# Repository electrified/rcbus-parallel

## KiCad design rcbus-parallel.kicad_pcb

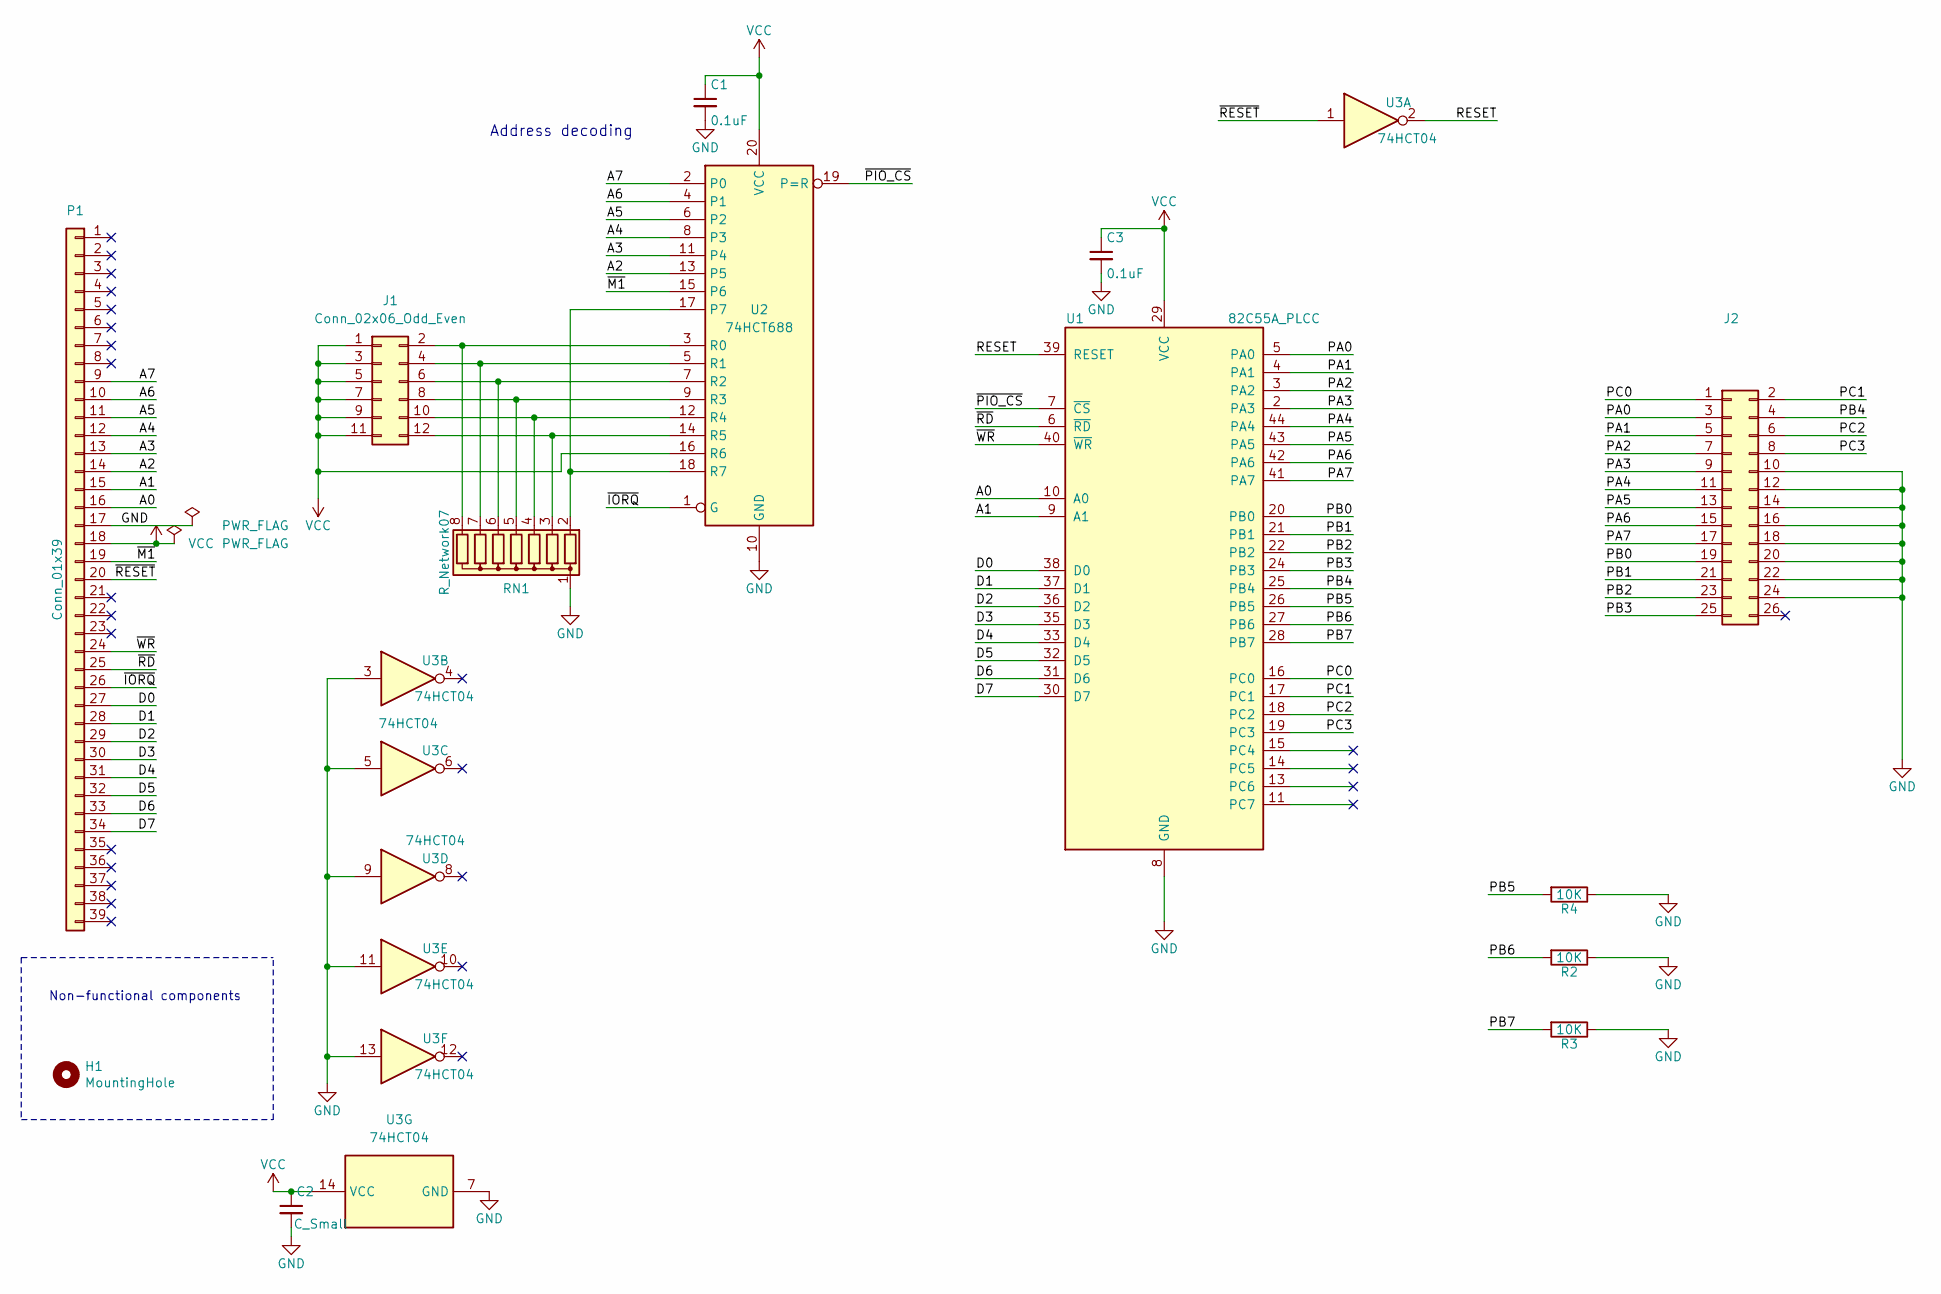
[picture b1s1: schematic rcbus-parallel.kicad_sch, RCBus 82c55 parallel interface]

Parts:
C1, C3: 0.1uF; C_Disc_D3.8mm_W2.6mm_P2.50mm
C2: C_Small; C_Disc_D3.8mm_W2.6mm_P2.50mm
H1: MountingHole; MountingHole_3.2mm_M3
J1: Conn_02x06_Odd_Even; PinHeader_2x06_P2.54mm_Vertical
J2: Conn_02x20_Odd_Even; IDC-Header_2x13_P2.54mm_Horizontal
P1: Conn_01x39; PinHeader_1x39_P2.54mm_Vertical
R2, R3, R4: 10K; R_Axial_DIN0207_L6.3mm_D2.5mm_P7.62mm_Horizontal
RN1: R_Network07; R_Array_SIP8
U1: 82C55A_PLCC; PLCC-44_THT-Socket
U2: 74HCT688; DIP-20_W7.62mm_Socket
U3: 74HCT04; DIP-14_W7.62mm_Socket

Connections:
/A0: P1.16, U1.10 (A0)
/A1: P1.15, U1.9 (A1)
/A2: P1.14, U2.13 (P5)
/A3: P1.13, U2.11 (P4)
/A4: P1.12, U2.8 (P3)
/A5: P1.11, U2.6 (P2)
/A6: P1.10, U2.4 (P1)
/A7: P1.9, U2.2 (P0)
/D0: P1.27, U1.38 (D0)
/D1: P1.28, U1.37 (D1)
/D2: P1.29, U1.36 (D2)
/D3: P1.30, U1.35 (D3)
/D4: P1.31, U1.33 (D4)
/D5: P1.32, U1.32 (D5)
/D6: P1.33, U1.31 (D6)
/D7: P1.34, U1.30 (D7)
/PA0: J2.3, U1.5 (PA0)
/PA1: J2.5, U1.4 (PA1)
/PA2: J2.7, U1.3 (PA2)
/PA3: J2.9, U1.2 (PA3)
/PA4: J2.11, U1.44 (PA4)
/PA5: J2.13, U1.43 (PA5)
/PA6: J2.15, U1.42 (PA6)
/PA7: J2.17, U1.41 (PA7)
/PB0: J2.19, U1.20 (PB0)
/PB1: J2.21, U1.21 (PB1)
/PB2: J2.23, U1.22 (PB2)
/PB3: J2.25, U1.24 (PB3)
/PB4: J2.4, U1.25 (PB4)
/PB5: R4.2, U1.26 (PB5)
/PB6: R2.2, U1.27 (PB6)
/PB7: R3.2, U1.28 (PB7)
/PC0: J2.1, U1.16 (PC0)
/PC1: J2.2, U1.17 (PC1)
/PC2: J2.6, U1.18 (PC2)
/PC3: J2.8, U1.19 (PC3)
/RESET: U1.39 (RESET), U3.2
/~IORQ: P1.26, U2.1 (G)
/~M1: P1.19, U2.15 (P6)
/~PIO_CS: U1.7 (~CS), U2.19 (P=R)
/~RD: P1.25, U1.6 (~RD)
/~RESET: P1.20, U3.1
/~WR: P1.24, U1.40 (~WR)
GND: C1.2, C2.2, C3.2, J2.10, J2.12, J2.14, J2.16, J2.18, J2.20, J2.22, J2.24, P1.17, R2.1, R3.1, R4.1, RN1.1 (common), U1.8 (GND), U2.10 (GND), U3.3, U3.5, U3.7 (GND), U3.9, U3.11, U3.13
unnamed: J1.2, RN1.8 (R7), U2.3 (R0)
unnamed: J1.4, RN1.7 (R6), U2.5 (R1)
unnamed: J1.6, RN1.6 (R5), U2.7 (R2)
unnamed: J1.8, RN1.5 (R4), U2.9 (R3)
unnamed: J1.10, RN1.4 (R3), U2.12 (R4)
unnamed: J1.12, RN1.3 (R2), U2.14 (R5)
unnamed: RN1.2 (R1), U2.17 (P7), U2.18 (R7)
VCC: C1.1, C2.1, C3.1, J1.1, J1.3, J1.5, J1.7, J1.9, J1.11, P1.18, U1.29 (VCC), U2.16 (R6), U2.20 (VCC), U3.14 (VCC)

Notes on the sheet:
Non-functional components
Address decoding

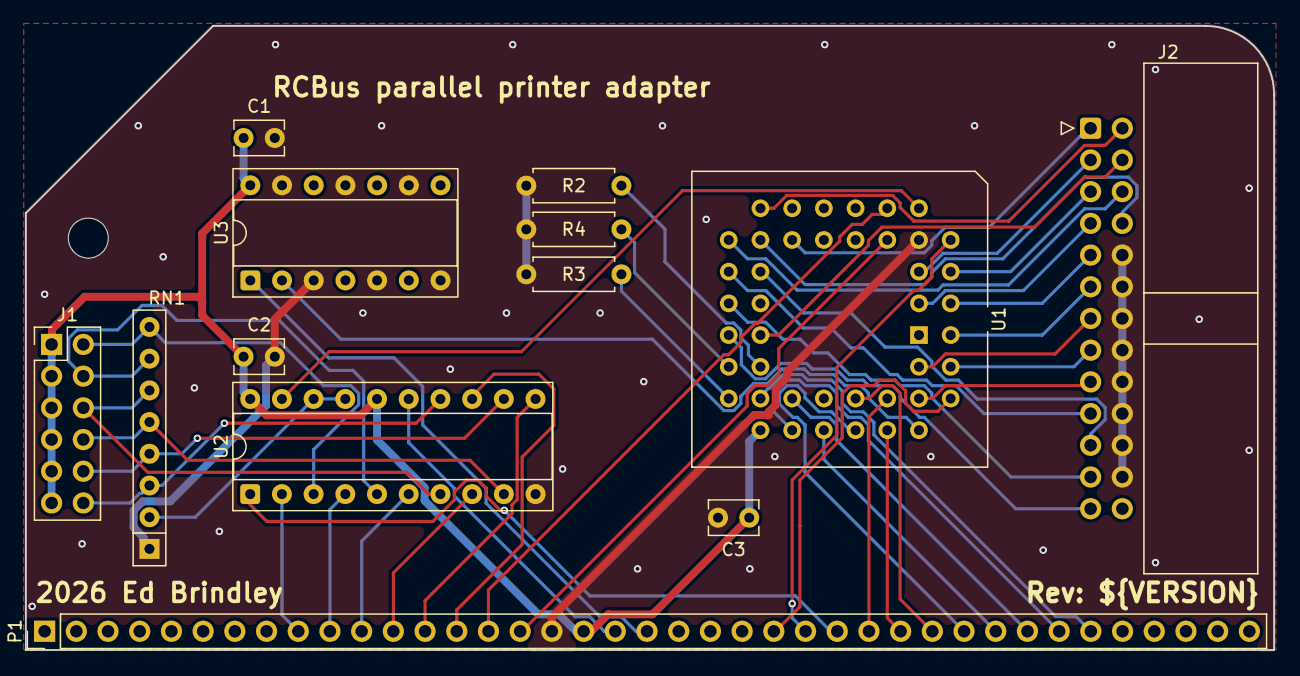
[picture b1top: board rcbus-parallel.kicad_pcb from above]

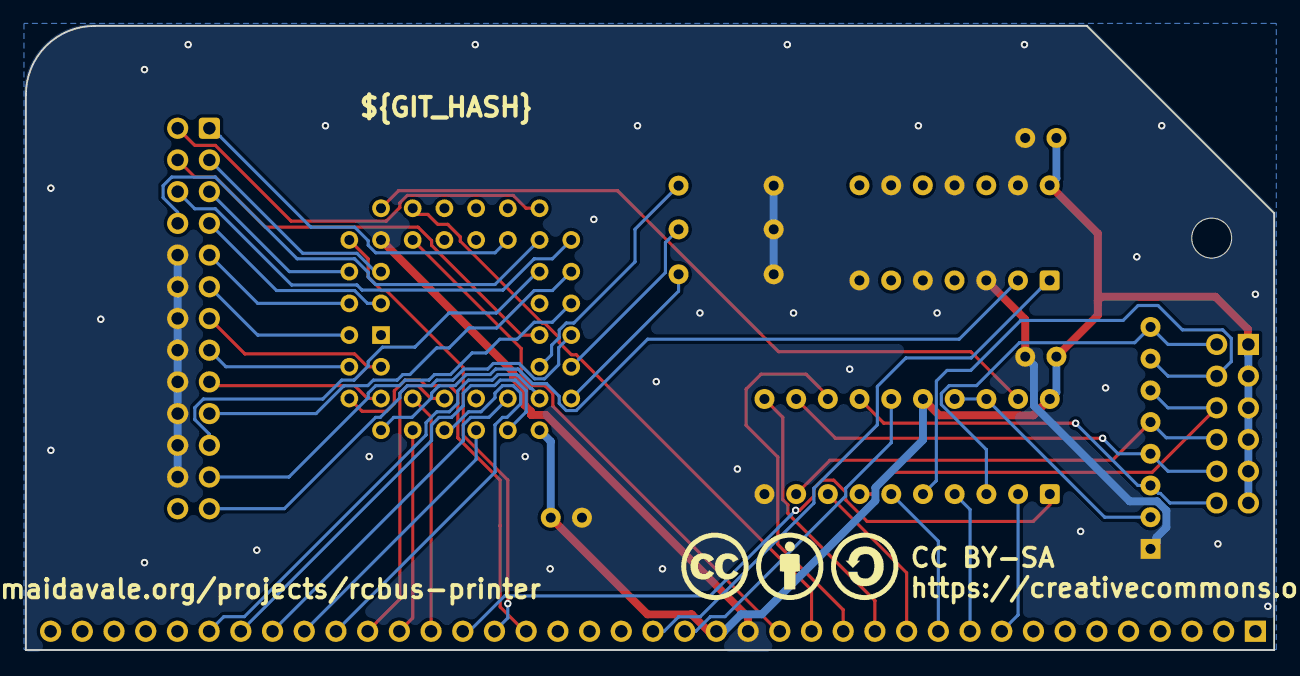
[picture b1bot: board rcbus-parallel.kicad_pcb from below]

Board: 2 copper layers, 100.0 x 50.0 mm, 17 parts (3 on the bottom side), 52 nets.

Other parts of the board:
G3: Symbol_CreativeCommons_Silk_Type2_Small
G4: Symbol_CC-Attribution_Silk_Small
G5: Symbol_CC-ShareAlike_Silk_Small

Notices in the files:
rcbus-parallel.kicad_pcb:
CC BY-SA
https://creativecommons.org
